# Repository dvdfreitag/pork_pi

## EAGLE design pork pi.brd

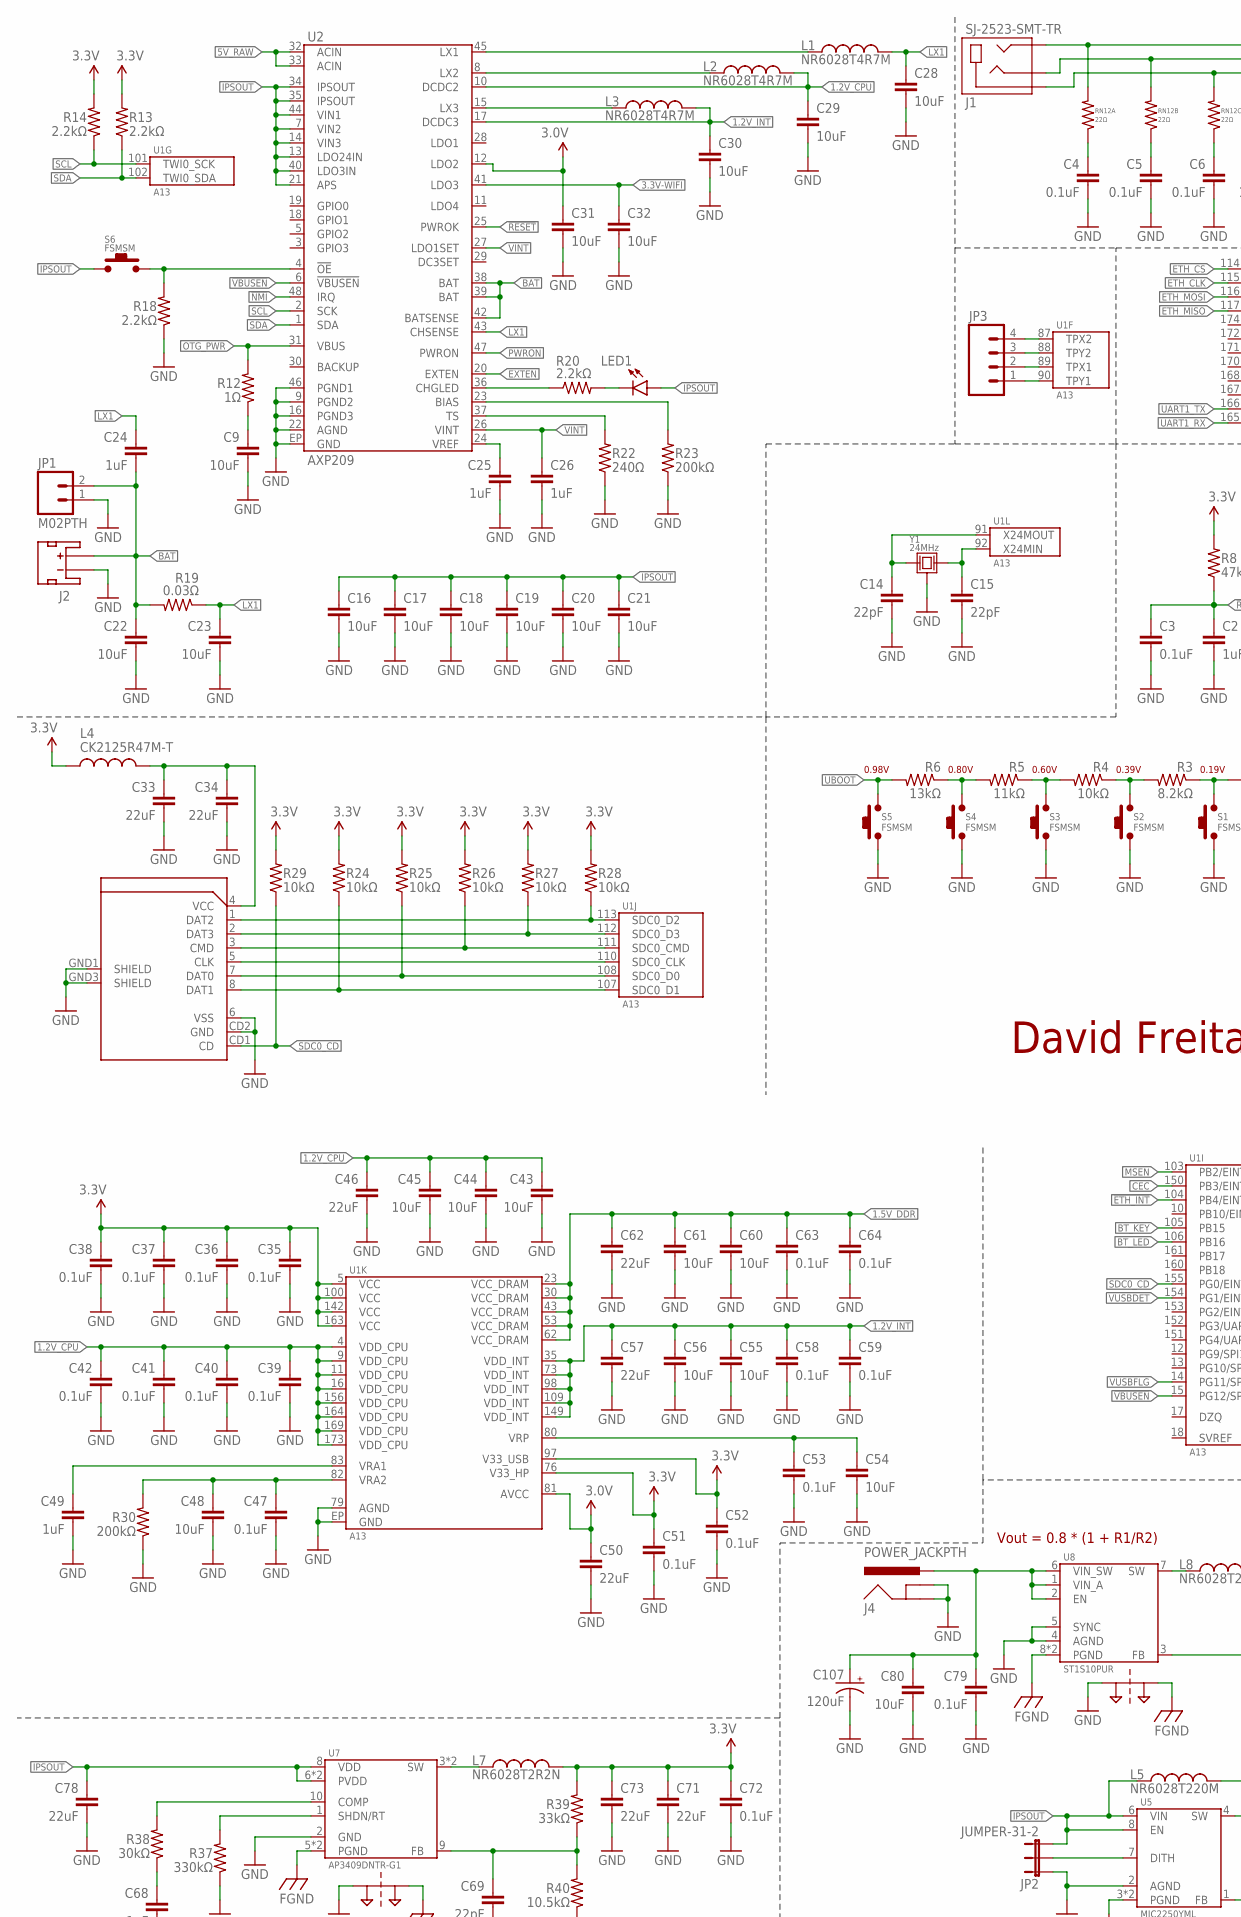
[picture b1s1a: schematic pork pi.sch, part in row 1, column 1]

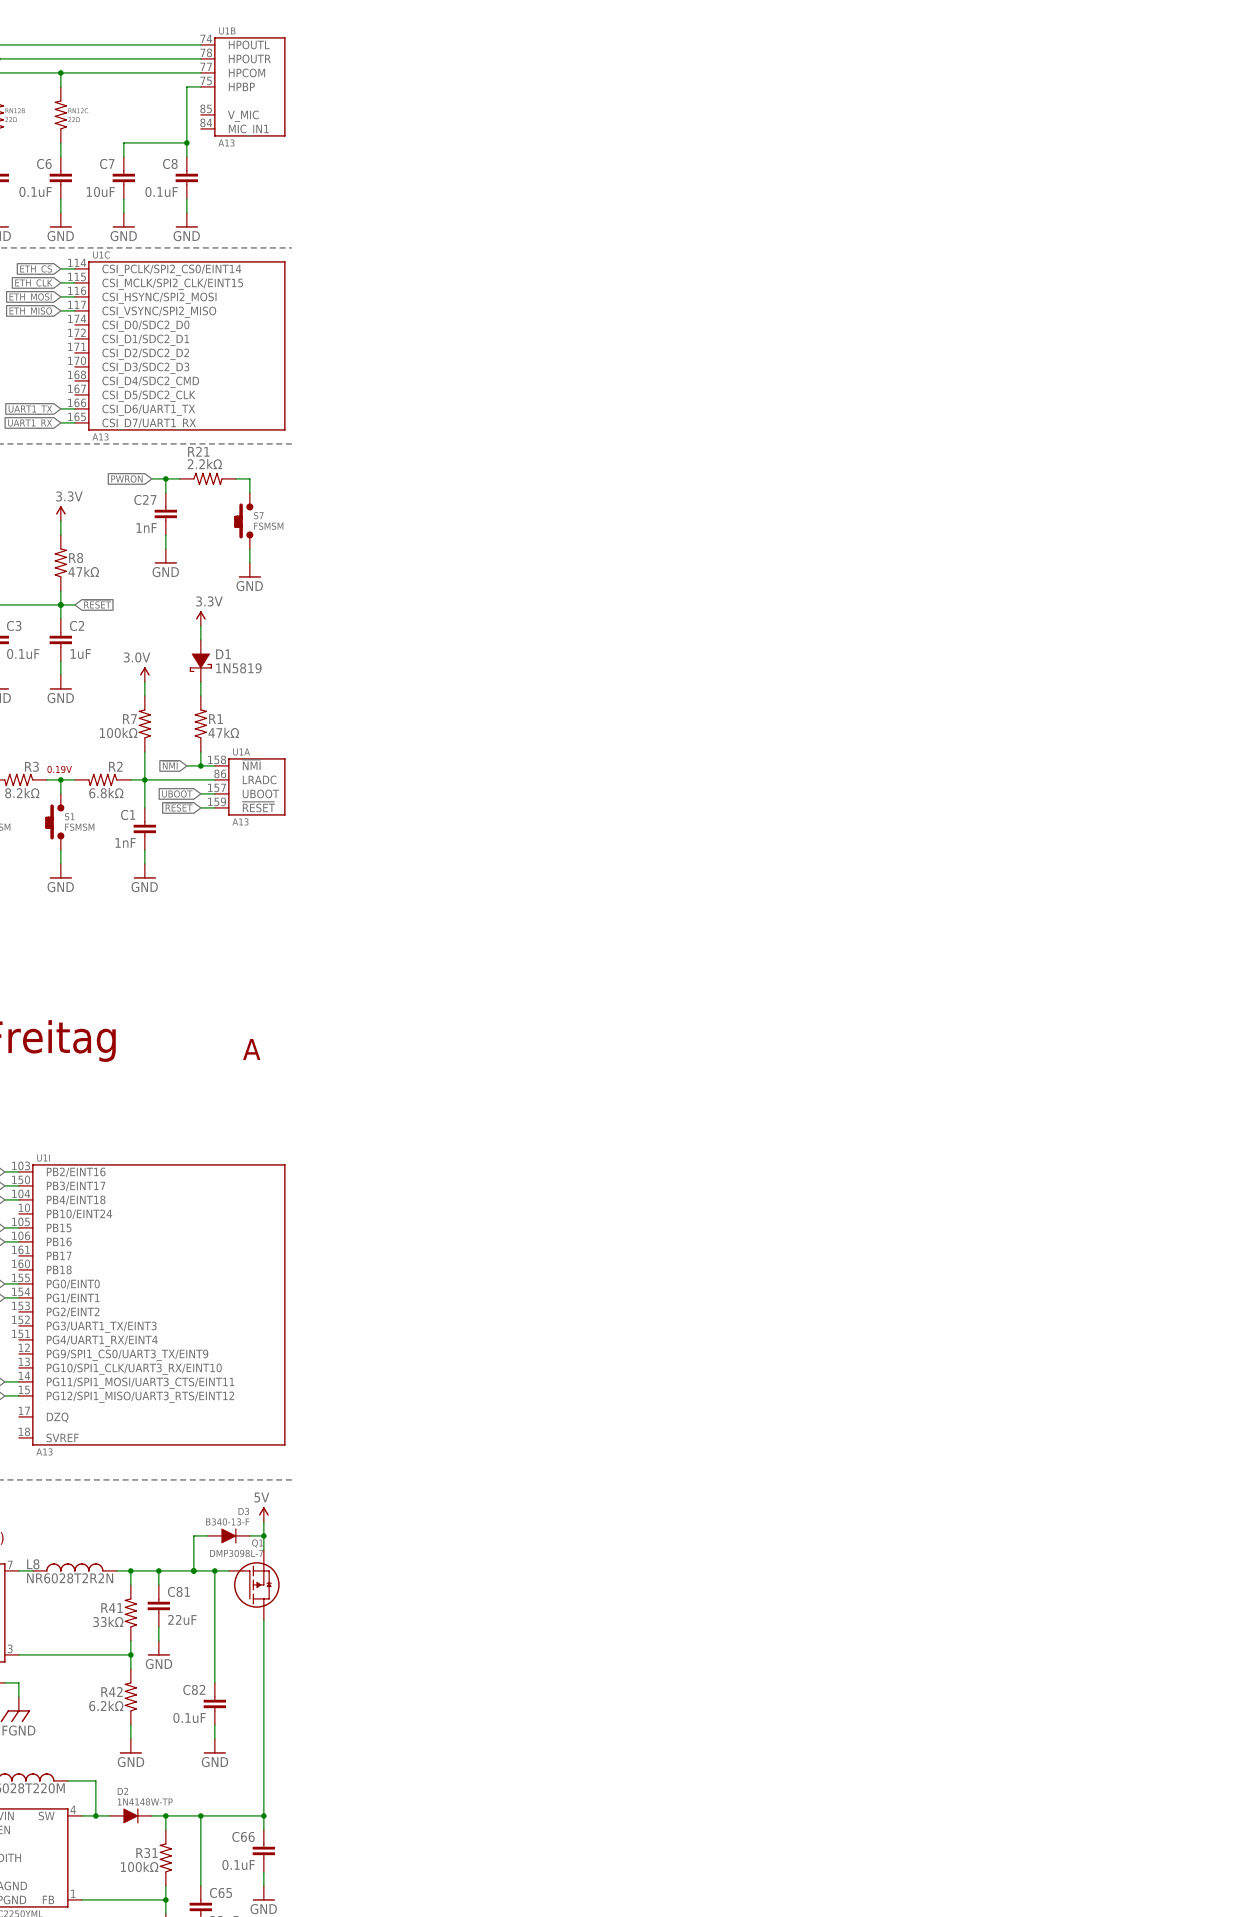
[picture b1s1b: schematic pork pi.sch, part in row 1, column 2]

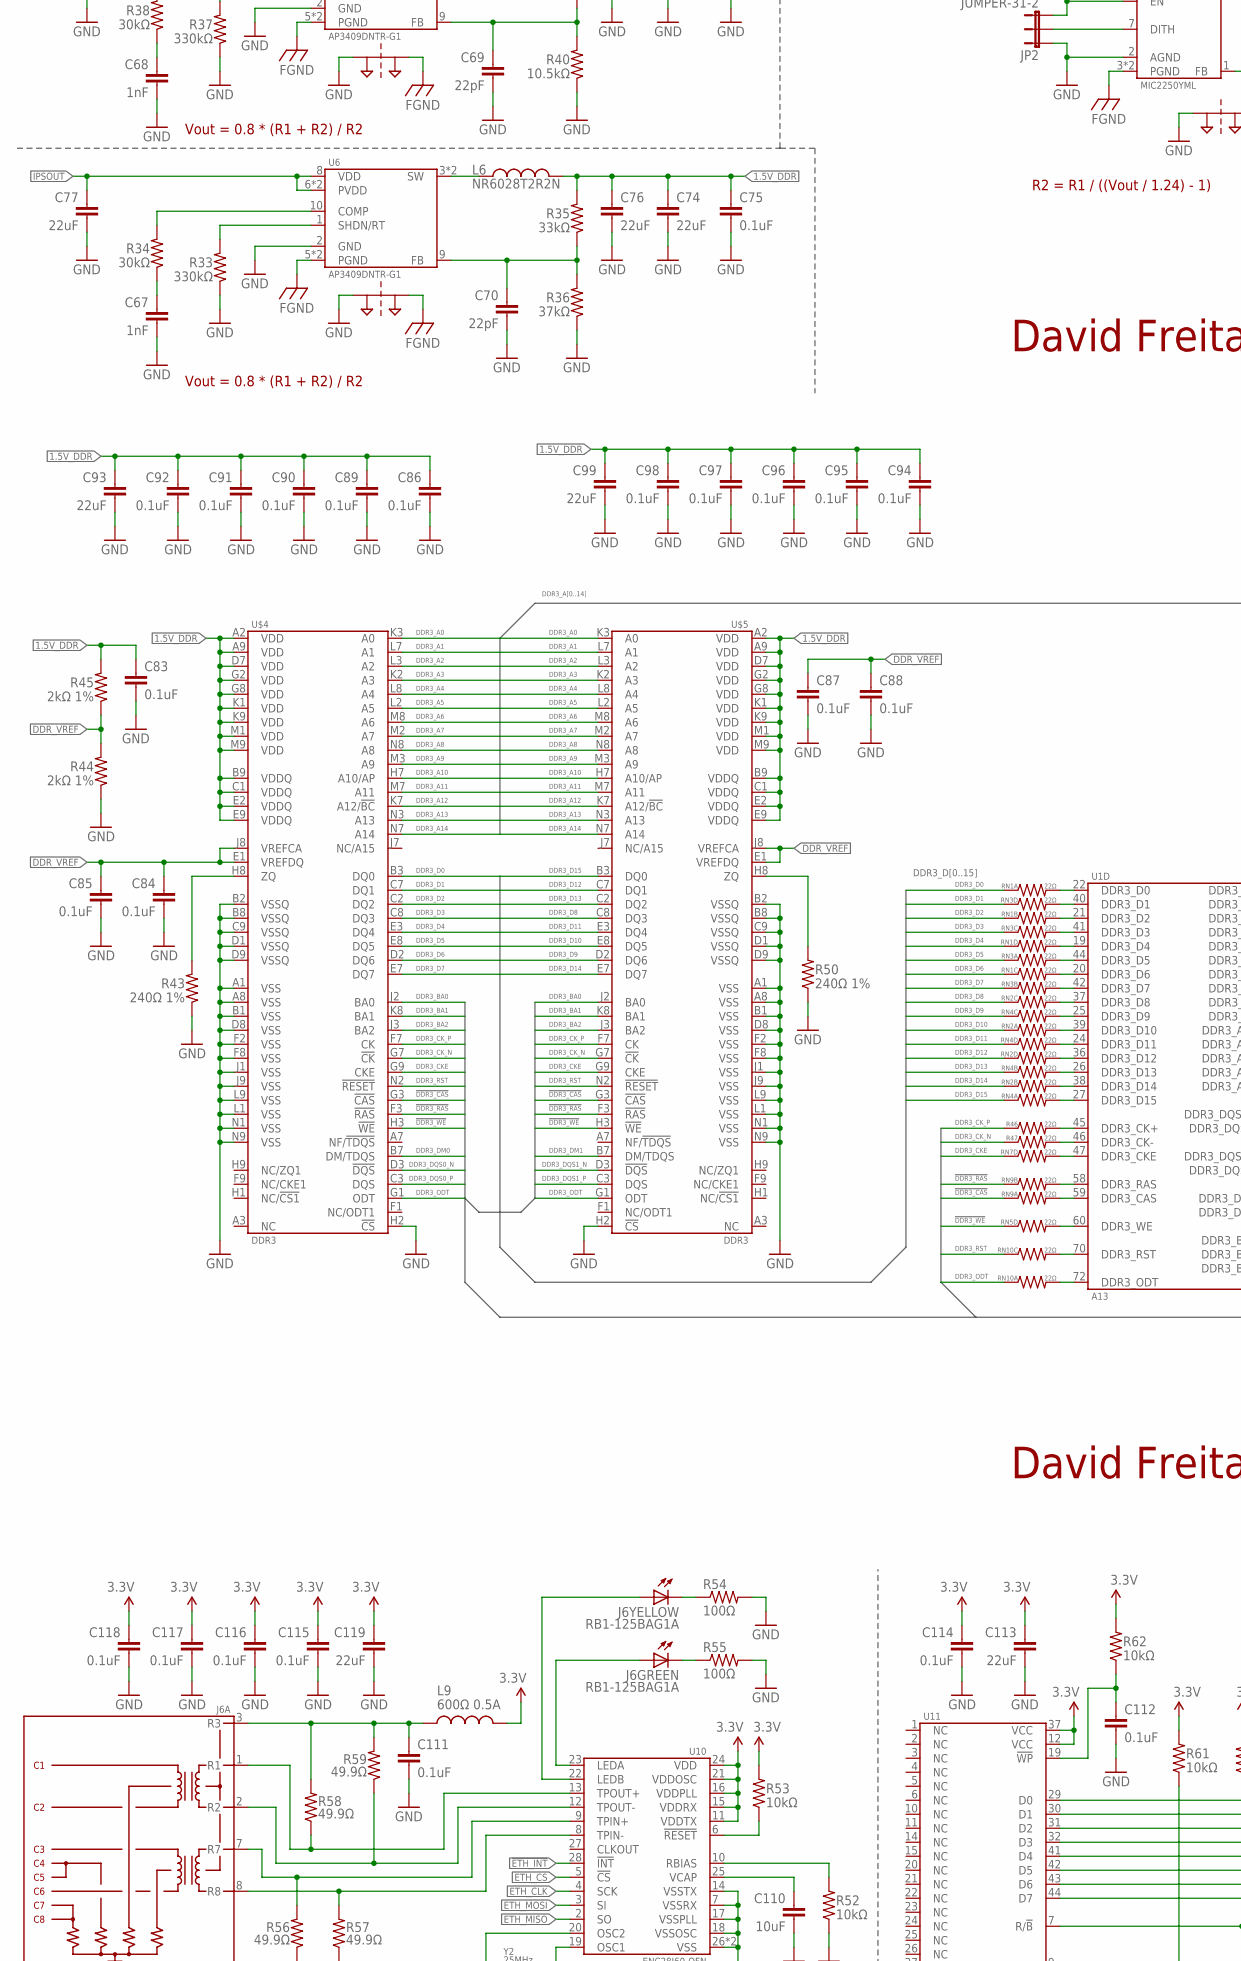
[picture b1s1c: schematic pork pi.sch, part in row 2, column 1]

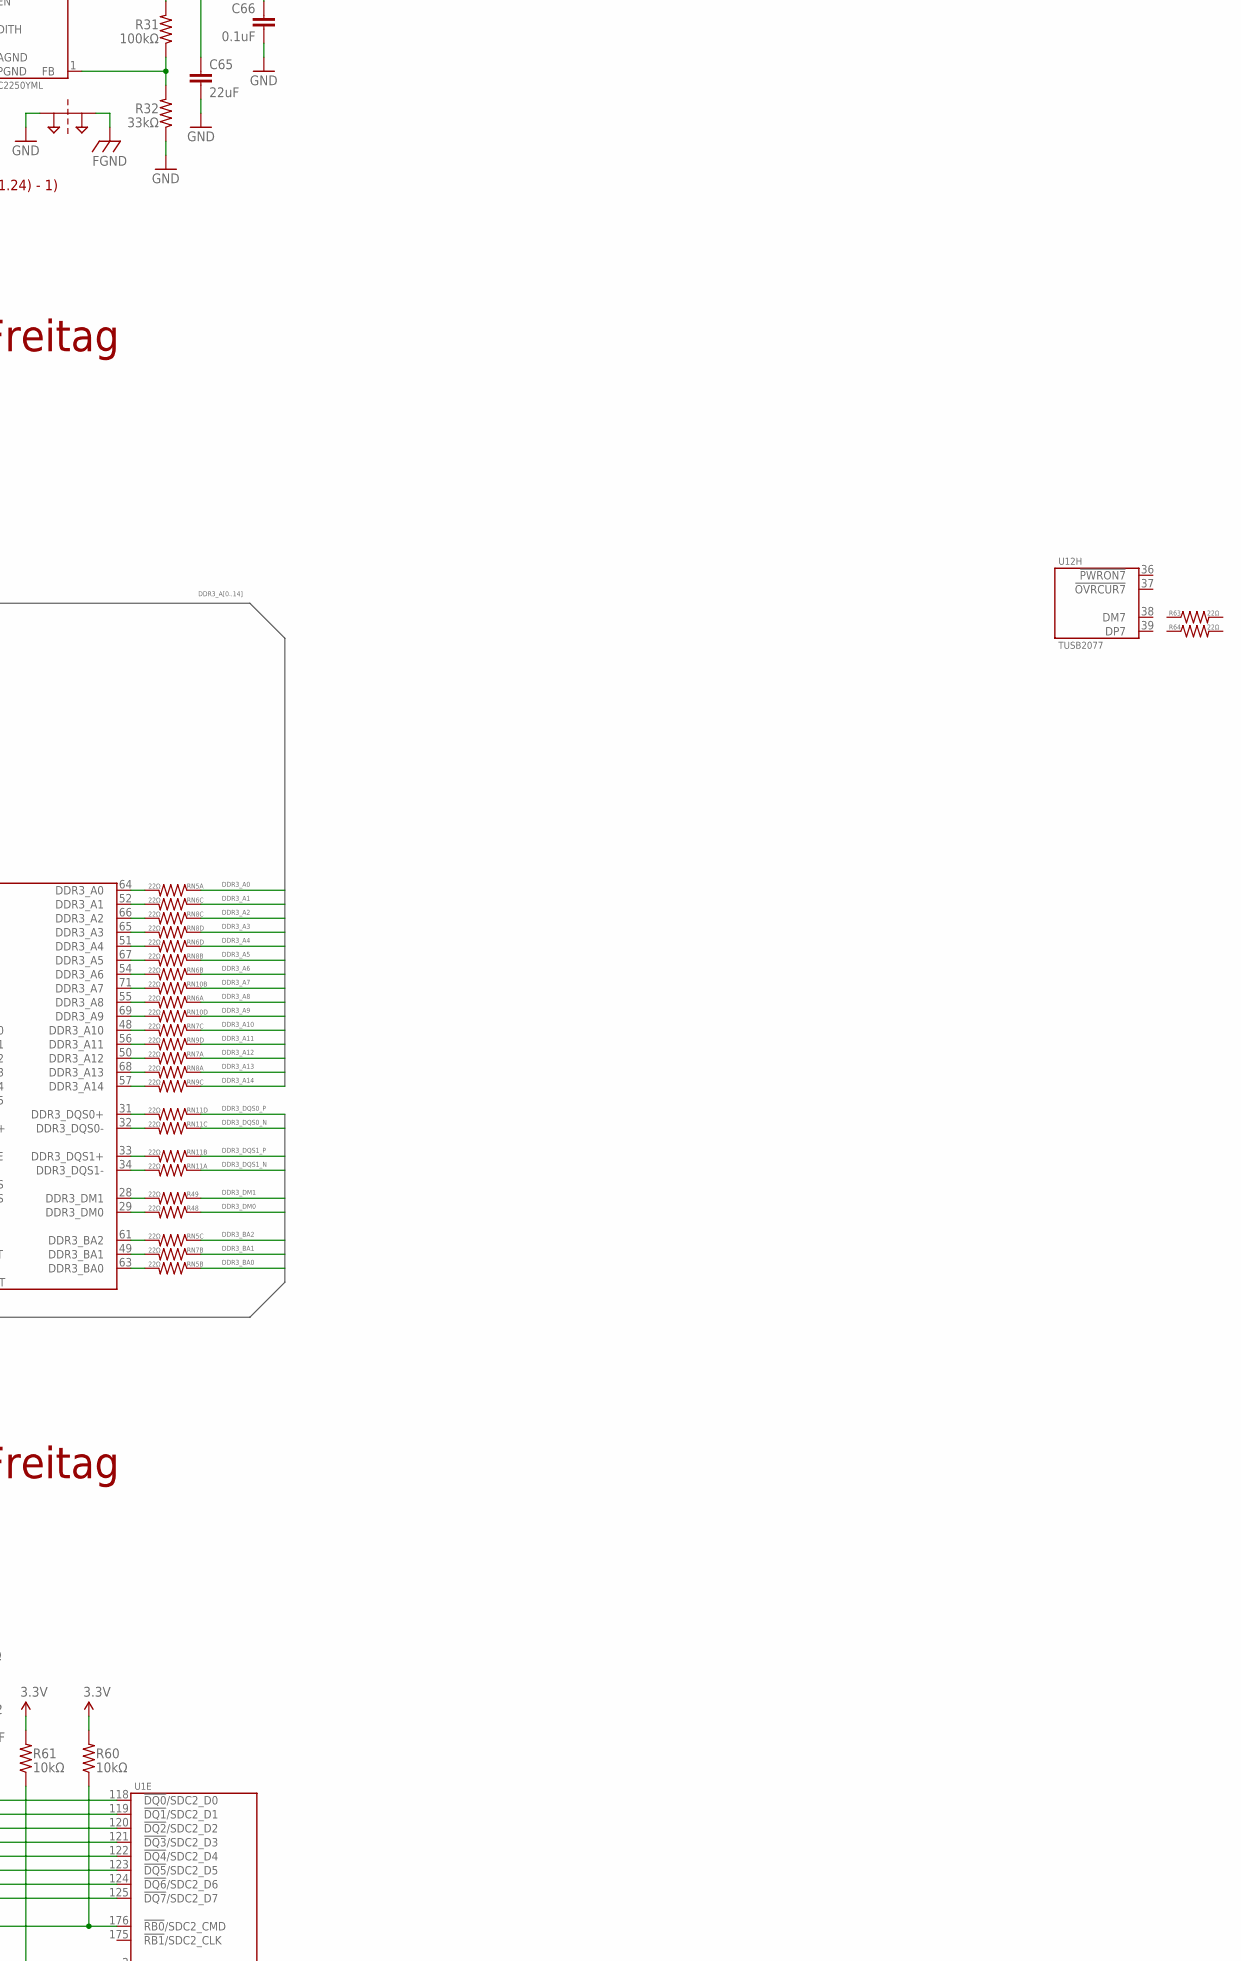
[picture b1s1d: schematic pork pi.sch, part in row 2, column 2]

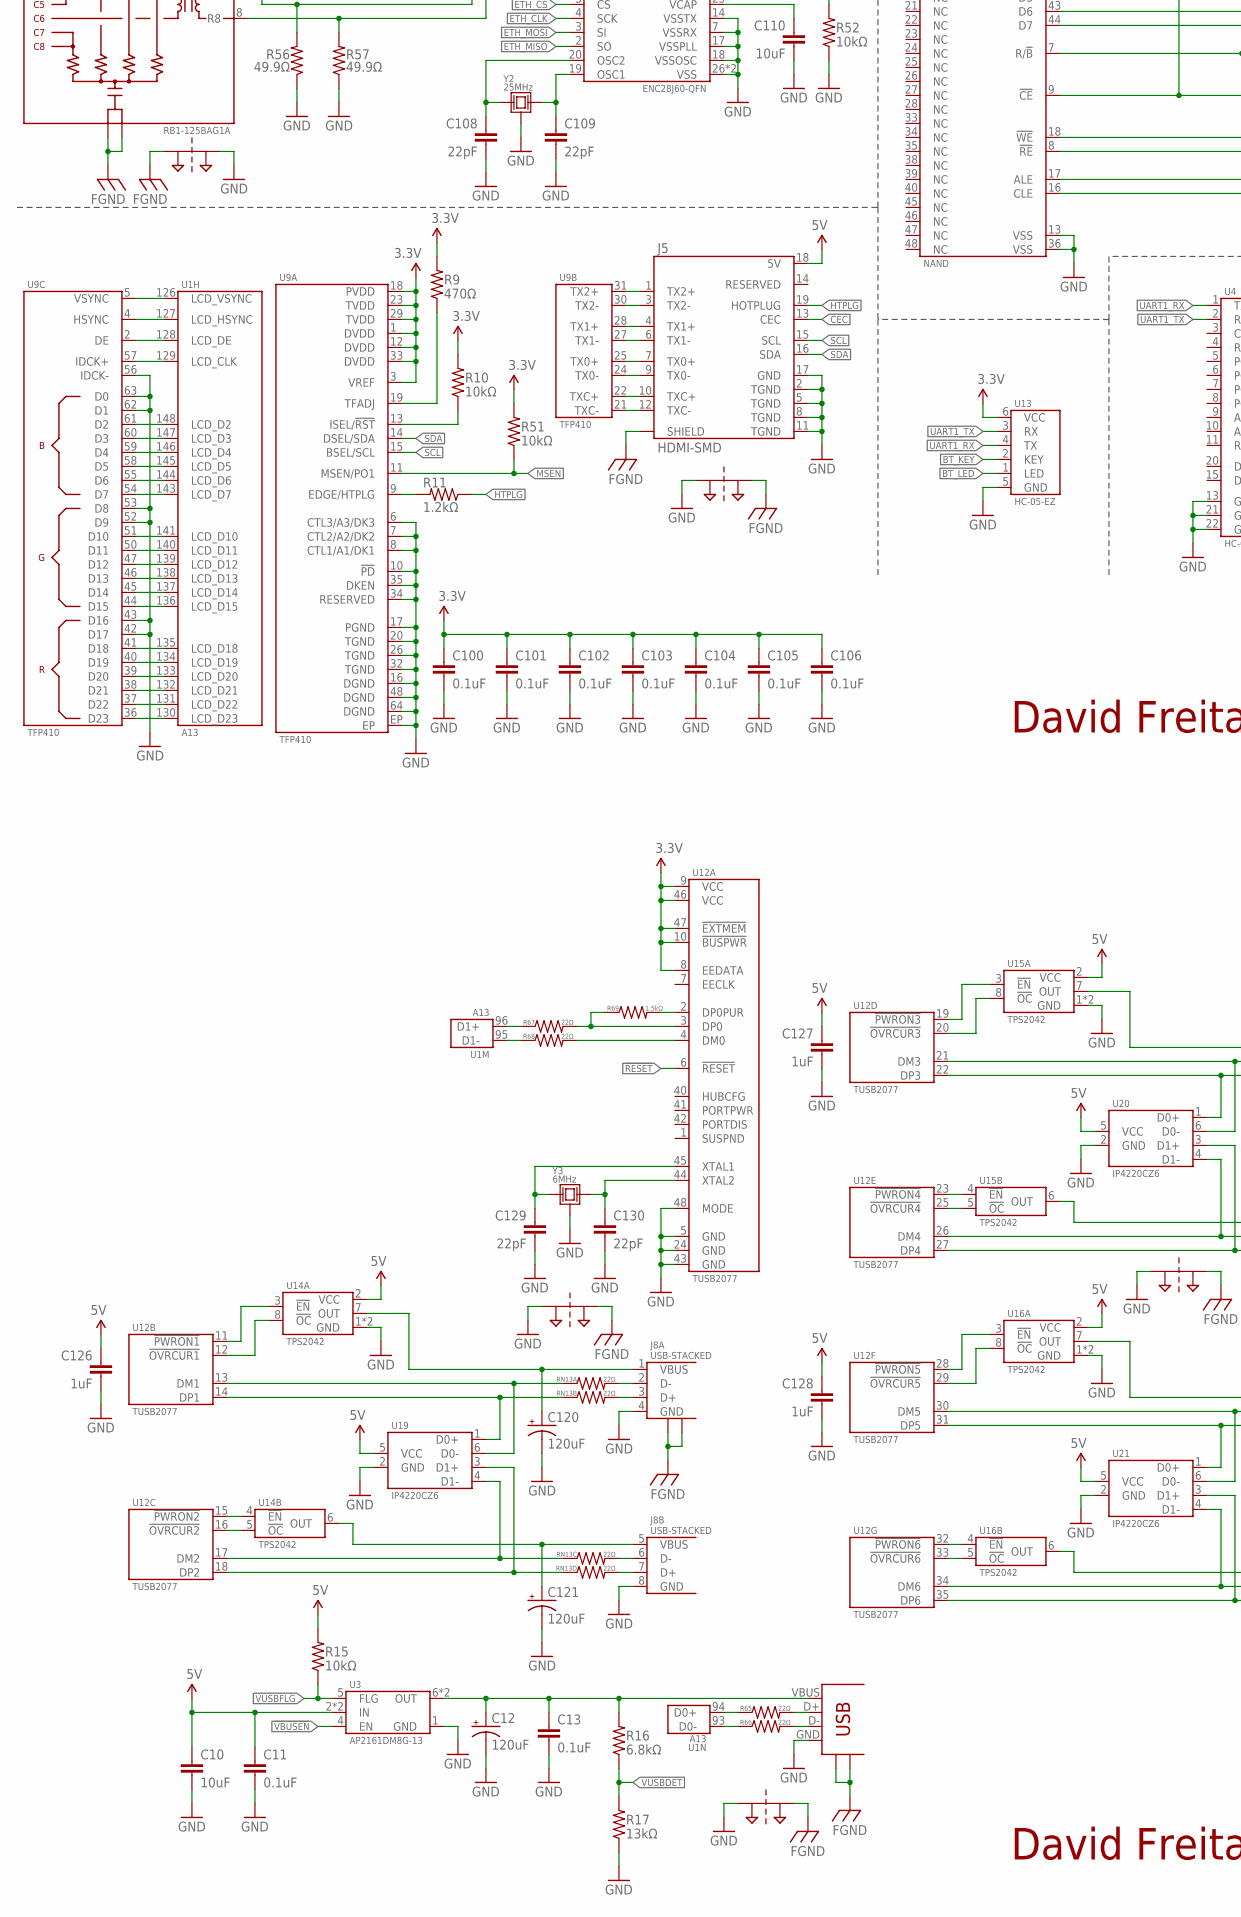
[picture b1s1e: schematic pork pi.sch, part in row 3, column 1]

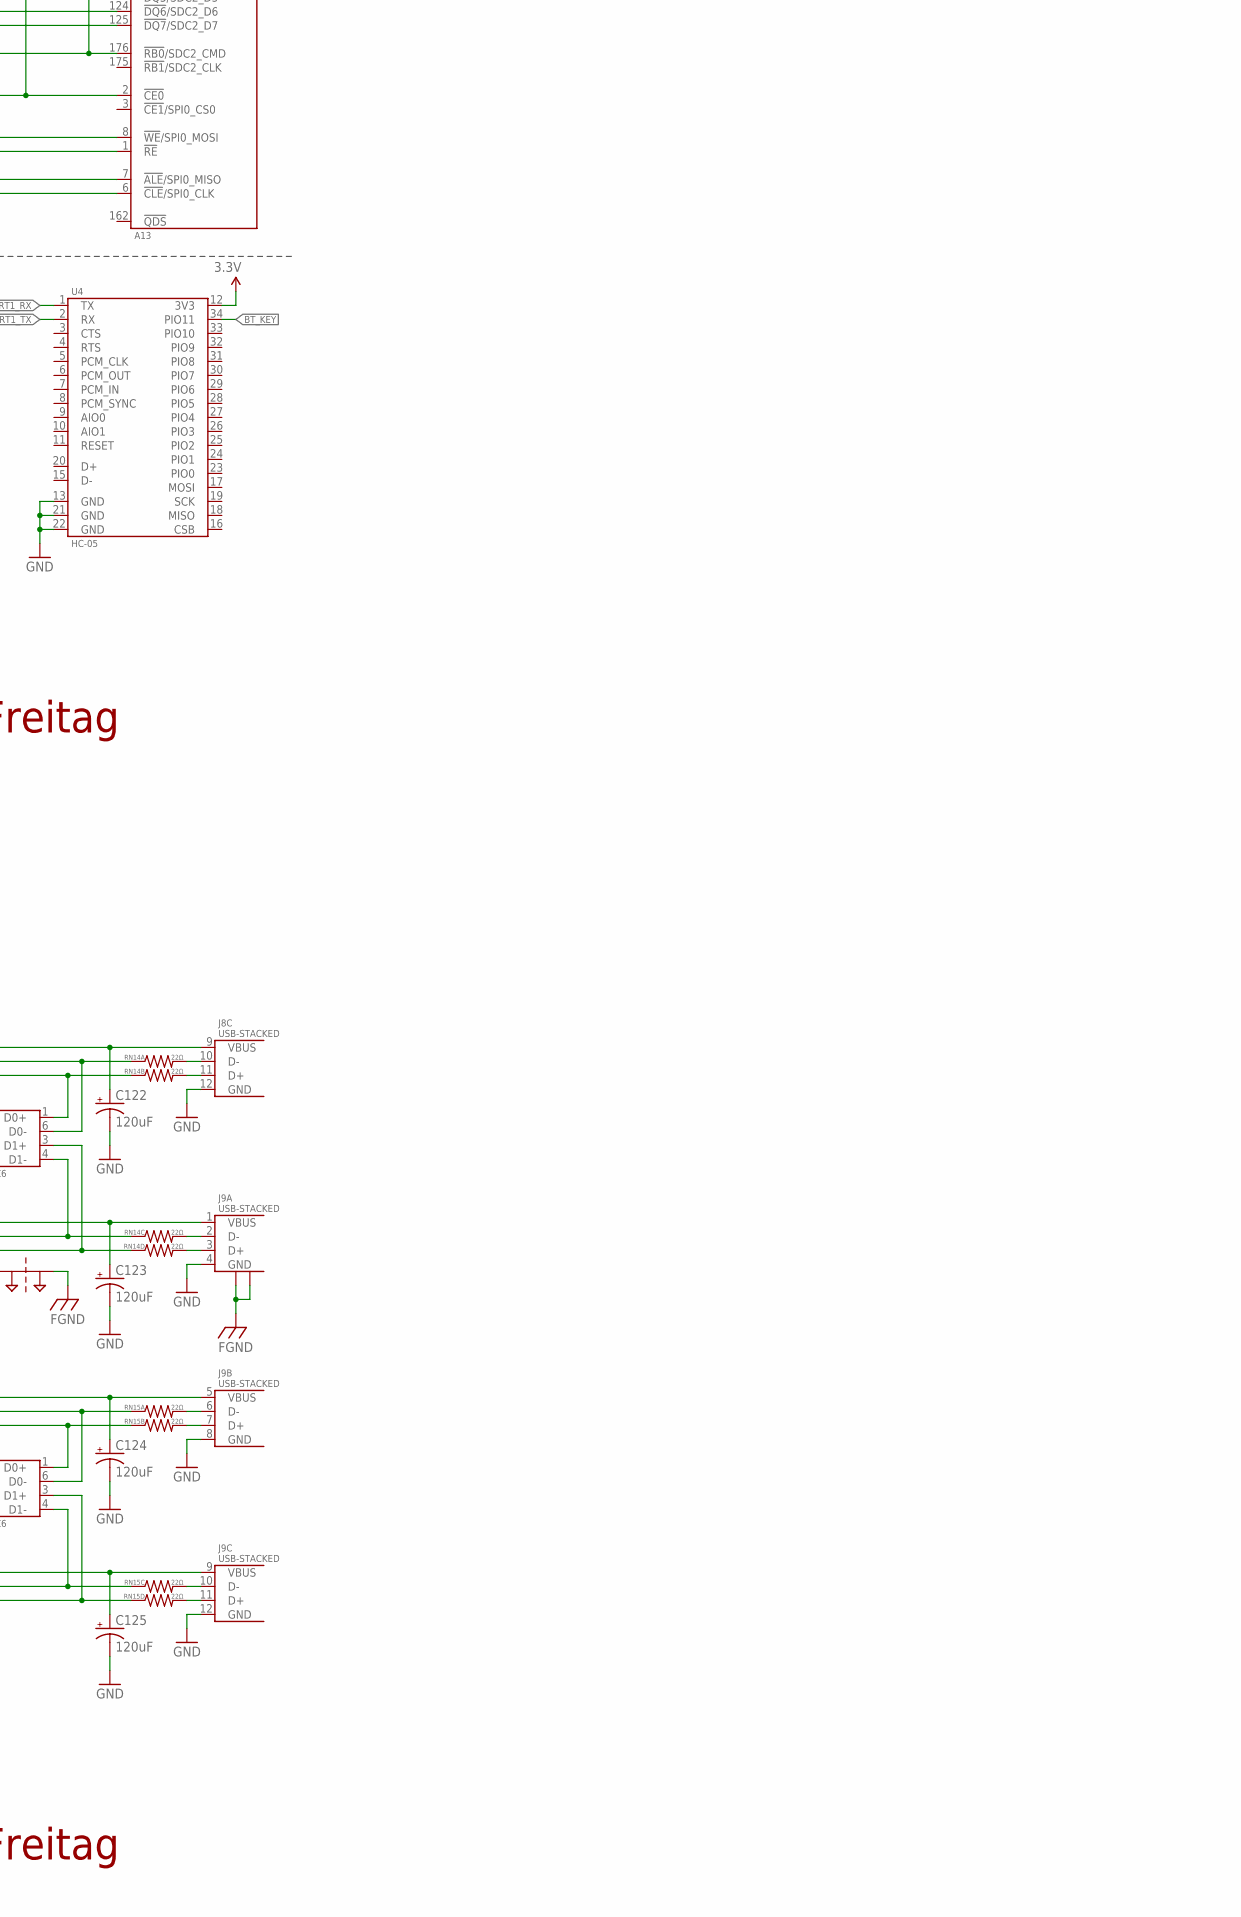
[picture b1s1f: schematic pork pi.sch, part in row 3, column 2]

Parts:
C1, C27, C67, C68: 1nF; 0402-CAP
C2, C24, C25, C26, C49, C126, C127, C128: 1uF; 0402-CAP
C3, C4, C5, C6, C8, C11, C13, C35, C36, C37, C38, C39, C40, C41, C42, C47, C51, C52, C53, C58, C59, C63, C64, C66, C72, C75, C79, C82, C83, C84, C85, C86, C87, C88, C89, C90, C91, C92, C94, C95, C96, C97, C98, C100, C101, C102, C103, C104, C105, C106, C111, C112, C114, C115, C116, C117, C118: 0.1uF; 0402-CAP
C7, C9, C10, C16, C17, C18, C19, C20, C21, C22, C23, C28, C29, C30, C31, C32, C43, C44, C45, C48, C54, C55, C56, C60, C61, C80, C110: 10uF; 0603-CAP
C12, C107, C120, C121, C122, C123, C124, C125: 120uF; CAP_POLYMER-6.5X6.5; PARTNUM 493-7371-1-ND
C14, C15, C69, C70, C108, C109, C129, C130: 22pF; 0402-CAP
C33, C34, C46, C50, C57, C62, C65, C71, C73, C74, C76, C77, C78, C81, C93, C99, C113, C119: 22uF; 0603-CAP
D1: 1N5819; SOD123
D2: 1N4148W-TP; SOD-123
D3: B340-13-F; SMC
J1: SJ-2523-SMT-TR
J2: JST_2MM_MALE; JST-2-SMD
J3: MICRO-SD; MICRO-SD-SOCKET-PP
J4: POWER_JACKPTH; POWER_JACK_PTH
J5: HDMI-SMD
J6: RB1-125BAG1A; ETHERNET
J7: USB+SHIELD-MICROB; USB-MICROB
J8, J9: USB-STACKED
JP1: M02PTH; 1X02
JP2: JUMPER-31-2; SJ_3_PASTE1&2
JP3: M04PTH; 1X04
L1, L2, L3: NR6028T4R7M
L4: CK2125R47M-T; 0805
L5: NR6028T220M; NR6028T4R7M
L6, L7, L8: NR6028T2R2N; NR6028T4R7M
L9: 600Ω 0.5A; 0805
LED1: LED1206; LED-1206
PT1, PT2, PT3, PT4, PT5, PT6, PT7, PT8, PT9: 2PT_GND_TIE
Q1: DMP3098L-7; SOT23-3
R1, R8: 47kΩ; 0402-RES
R2, R16: 6.8kΩ; 0402-RES
R3: 8.2kΩ; 0402-RES
R4, R10, R15, R24, R25, R26, R27, R28, R29, R51, R52, R53, R60, R61, R62: 10kΩ; 0402-RES
R5: 11kΩ; 0402-RES
R6, R17: 13kΩ; 0402-RES
R7, R31: 100kΩ; 0402-RES
R9: 470Ω; 0402-RES
R11: 1.2kΩ; 0402-RES
R12: 1Ω; 0402-RES
R13, R14, R18, R20, R21: 2.2kΩ; 0402-RES
R19: 0.03Ω; 0805
R22: 240Ω; 0402-RES
R23, R30: 200kΩ; 0402-RES
R32, R35, R39, R41: 33kΩ; 0402-RES
R33, R37: 330kΩ; 0402-RES
R34, R38: 30kΩ; 0402-RES
R36: 37kΩ; 0402-RES
R40: 10.5kΩ; 0402-RES
R42: 6.2kΩ; 0402-RES
R43, R50: 240Ω 1%; 0402-RES
R44, R45: 2kΩ 1%; 0402-RES
R46, R47, R48, R49, R63, R64, R65, R66, R67, R68: 22Ω; 0402-RES
R54, R55: 100Ω; 0402-RES
R56, R57, R58, R59: 49.9Ω; 0805
R69: 1.5kΩ; 0402-RES
RN1, RN2, RN3, RN4, RN5, RN6, RN7, RN8, RN9, RN10, RN11, RN12, RN13, RN14, RN15: 22Ω; RESISTOR_NETWORK-1206
S1, S2, S3, S4, S5, S6, S7: FSMSM
U1: A13
U2: AXP209; QFN-48
U3: AP2161DM8G-13; MSOP-8
U4: HC-05
U5: MIC2250YML; MLF-8
U6, U7: AP3409DNTR-G1; UDFN-10
U8: ST1S10PUR; DFN-8
U9: TFP410; PQFP-64
U10: ENC28J60-QFN; QFN-28
U11: NAND; TSOP1-48
U12: TUSB2077; LQFP-48
U13: HC-05-EZ; M06X1
U14, U15, U16: TPS2042; SON-8
U19, U20, U21: IP4220CZ6; SOT-6
U$4, U$5: DDR3; DDR3_78
Y1: 24MHz; FA-238
Y2: 25MHz; FA-238
Y3: 6MHz; FA-238

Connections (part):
1.2V_CPU: C29.1, C39.1, C40.1, C41.1, C42.1, C43.1, C44.1, C45.1, C46.1, L2.2, U1.4 (VDD_CPU), U1.9 (VDD_CPU), U1.11 (VDD_CPU), U1.16 (VDD_CPU), U1.156 (VDD_CPU), U1.164 (VDD_CPU), U1.169 (VDD_CPU), U1.173 (VDD_CPU), U2.10 (DCDC2)
1.2V_INT: C30.1, C55.1, C56.1, C57.1, C58.1, C59.1, L3.2, U1.35 (VDD_INT), U1.73 (VDD_INT), U1.98 (VDD_INT), U1.109 (VDD_INT), U1.149 (VDD_INT), U2.17 (DCDC3)
1.5V_DDR: C60.1, C61.1, C62.1, C63.1, C64.1, C74.1, C75.1, C76.1, C83.1, C86.1, C89.1, C90.1, C91.1, C92.1, C93.1, C94.1, C95.1, C96.1, C97.1, C98.1, C99.1, L6.2, R35.2, R45.2, U1.23 (VCC_DRAM), U1.30 (VCC_DRAM), U1.43 (VCC_DRAM), U1.53 (VCC_DRAM), U1.62 (VCC_DRAM), U$4.A2 (VDD), U$4.A9 (VDD), U$4.B9 (VDDQ), U$4.C1 (VDDQ), U$4.D7 (VDD), U$4.E2 (VDDQ), U$4.E9 (VDDQ), U$4.G2 (VDD), U$4.G8 (VDD), U$4.K1 (VDD), U$4.K9 (VDD), U$4.M1 (VDD), U$4.M9 (VDD), U$5.A2 (VDD), U$5.A9 (VDD), U$5.B9 (VDDQ), U$5.C1 (VDDQ), U$5.D7 (VDD), U$5.E2 (VDDQ), U$5.E9 (VDDQ), U$5.G2 (VDD), U$5.G8 (VDD), U$5.K1 (VDD), U$5.K9 (VDD), U$5.M1 (VDD), U$5.M9 (VDD)
3.0V: C31.1, C50.1, R7.2, U1.81 (AVCC), U2.12 (LDO2)
3.3V: C35.1, C36.1, C37.1, C38.1, C51.1, C52.1, C71.1, C72.1, C73.1, C100.1, C101.1, C102.1, C103.1, C104.1, C105.1, C106.1, C113.1, C114.1, C115.1, C116.1, C117.1, C118.1, C119.1, D1.ANODE, L4.1, L7.2, L9.2, R8.2, R9.2, R10.2, R13.2, R14.2, R24.2, R25.2, R26.2, R27.2, R28.2, R29.2, R39.2, R51.2, R53.2, R60.2, R61.2, R62.2, U1.5 (VCC), U1.76 (V33_HP), U1.97 (V33_USB), U1.100 (VCC), U1.142 (VCC), U1.163 (VCC), U4.12 (3V3), U9.1 (DVDD), U9.3 (VREF), U9.12 (DVDD), U9.18 (PVDD), U9.23 (TVDD), U9.29 (TVDD), U9.33 (DVDD), U10.11 (VDDTX), U10.15 (VDDRX), U10.16 (VDDPLL), U10.21 (VDDOSC), U10.24 (VDD), U11.12 (VCC), U11.37 (VCC), U12.8 (EEDATA), U12.9 (VCC), U12.10 (!BUSPWR), U12.46 (VCC), U12.47 (!EXTMEM), U13.6 (VCC)
3.3V-WIFI: C32.1, U2.41 (LDO3)
5V: C10.1, C11.1, C126.1, C127.1, C128.1, D3.C, J5.18 (5V), Q1.2 (S), R15.2, U3.2 (IN), U3.3 (IN), U14.2 (VCC), U15.2 (VCC), U16.2 (VCC), U19.5 (VCC), U20.5 (VCC), U21.5 (VCC)
5V_RAW: U2.32 (ACIN), U2.33 (ACIN)
!DDR3_CAS!: RN9.1, U$4.G3 (!CAS), U$5.G3 (!CAS)
!DDR3_RAS!: RN9.2 (1), U$4.F3 (!RAS), U$5.F3 (!RAS)
!DDR3_WE!: RN5.4 (1), U$4.H3 (!WE), U$5.H3 (!WE)
!ETH_INT: U1.104 (PB4/EINT18), U10.28 (!INT)
!NMI: R1.1, U1.158 (!NMI), U2.48 (IRQ)
!RESET: C2.1, C3.1, R8.1, U1.159 (!RESET), U2.25 (PWROK), U12.6 (!RESET)
!VBUSEN: U1.15 (PG12/SPI1_MISO/UART3_RTS/EINT12), U2.6 (!VBUSEN), U3.4 (EN)
BAT: C22.1, C24.2, J2.2 (+), JP1.2, R19.2, U2.38 (BAT), U2.39 (BAT), U2.42 (BATSENSE)
BT_KEY: U1.105 (PB15), U4.34 (PIO11), U13.2 (KEY)
BT_LED: U1.106 (PB16), U13.1 (LED)
CEC: J5.13 (CEC), U1.150 (PB3/EINT17)
D0_N: R66.1, U1.93 (D0-)
D0_P: R65.1, U1.94 (D0+)
D1_N: R68.1, U1.95 (D1-)
D1_P: R67.1, U1.96 (D1+)
D2_N: RN13.1, U12.13 (DM1), U19.6 (D0-)
D2_P: RN13.2 (1), U12.14 (DP1), U19.1 (D0+)
D3_N: RN13.3 (1), U12.17 (DM2), U19.4 (D1-)
D3_P: RN13.4 (1), U12.18 (DP2), U19.3 (D1+)
D4_N: RN14.1, U12.21 (DM3), U20.6 (D0-)
D4_P: RN14.2 (1), U12.22 (DP3), U20.1 (D0+)
D5_N: RN14.3 (1), U12.26 (DM4), U20.4 (D1-)
D5_P: RN14.4 (1), U12.27 (DP4), U20.3 (D1+)
D6_N: RN15.1, U12.30 (DM5), U21.6 (D0-)
D6_P: RN15.2 (1), U12.31 (DP5), U21.1 (D0+)
D7_N: RN15.3 (1), U12.34 (DM6), U21.4 (D1-)
D7_P: RN15.4 (1), U12.35 (DP6), U21.3 (D1+)
DDR3_A0: RN5.1, U$4.K3 (A0), U$5.K3 (A0)
DDR3_A1: RN6.3 (1), U$4.L7 (A1), U$5.L7 (A1)
DDR3_A2: RN8.3 (1), U$4.L3 (A2), U$5.L3 (A2)
DDR3_A3: RN8.4 (1), U$4.K2 (A3), U$5.K2 (A3)
DDR3_A4: RN6.4 (1), U$4.L8 (A4), U$5.L8 (A4)
DDR3_A5: RN8.2 (1), U$4.L2 (A5), U$5.L2 (A5)
DDR3_A6: RN6.2 (1), U$4.M8 (A6), U$5.M8 (A6)
DDR3_A7: RN10.2 (1), U$4.M2 (A7), U$5.M2 (A7)
DDR3_A8: RN6.1, U$4.N8 (A8), U$5.N8 (A8)
DDR3_A9: RN10.4 (1), U$4.M3 (A9), U$5.M3 (A9)
DDR3_A10: RN7.3 (1), U$4.H7 (A10/AP), U$5.H7 (A10/AP)
DDR3_A11: RN9.4 (1), U$4.M7 (A11), U$5.M7 (A11)
DDR3_A12: RN7.1, U$4.K7 (A12/!BC), U$5.K7 (A12/!BC)
DDR3_A13: RN8.1, U$4.N3 (A13), U$5.N3 (A13)
DDR3_A14: RN9.3 (1), U$4.N7 (A14), U$5.N7 (A14)
DDR3_BA0: RN5.2 (1), U$4.J2 (BA0), U$5.J2 (BA0)
DDR3_BA1: RN7.2 (1), U$4.K8 (BA1), U$5.K8 (BA1)
DDR3_BA2: RN5.3 (1), U$4.J3 (BA2), U$5.J3 (BA2)
DDR3_CKE: RN7.4 (1), U$4.G9 (CKE), U$5.G9 (CKE)
DDR3_CK_N: R47.1, U$4.G7 (!CK), U$5.G7 (!CK)
DDR3_CK_P: R46.1, U$4.F7 (CK), U$5.F7 (CK)
DDR3_D0: RN1.1, U$4.B3 (DQ0)
DDR3_D1: RN3.4 (1), U$4.C7 (DQ1)
DDR3_D2: RN1.2 (1), U$4.C2 (DQ2)
DDR3_D3: RN3.3 (1), U$4.C8 (DQ3)
DDR3_D4: RN1.4 (1), U$4.E3 (DQ4)
DDR3_D5: RN3.1, U$4.E8 (DQ5)
DDR3_D6: RN1.3 (1), U$4.D2 (DQ6)
DDR3_D7: RN3.2 (1), U$4.E7 (DQ7)
DDR3_D8: RN2.3 (1), U$5.C8 (DQ3)
DDR3_D9: RN4.3 (1), U$5.D2 (DQ6)
DDR3_D10: RN2.1, U$5.E8 (DQ5)
DDR3_D11: RN4.4 (1), U$5.E3 (DQ4)
DDR3_D12: RN2.4 (1), U$5.C7 (DQ1)
DDR3_D13: RN4.2 (1), U$5.C2 (DQ2)
DDR3_D14: RN2.2 (1), U$5.E7 (DQ7)
DDR3_D15: RN4.1, U$5.B3 (DQ0)
DDR3_DM0: R48.1, U$4.B7 (DM/TDQS)
DDR3_DM1: R49.1, U$5.B7 (DM/TDQS)
DDR3_DQS0_N: RN11.3 (1), U$4.D3 (!DQS)
DDR3_DQS0_P: RN11.4 (1), U$4.C3 (DQS)
DDR3_DQS1_N: RN11.1, U$5.D3 (!DQS)
DDR3_DQS1_P: RN11.2 (1), U$5.C3 (DQS)
DDR3_ODT: RN10.1, U$4.G1 (ODT), U$5.G1 (ODT)
DDR3_RST: RN10.3 (1), U$4.N2 (!RESET), U$5.N2 (!RESET)
DDR_VREF: C84.1, C85.1, C87.1, C88.1, R44.2, R45.1, U$4.E1 (VREFDQ), U$4.J8 (VREFCA), U$5.E1 (VREFDQ), U$5.J8 (VREFCA)
ETH_CLK: U1.115 (CSI_MCLK/SPI2_CLK/EINT15), U10.4 (SCK)
ETH_CS: U1.114 (CSI_PCLK/SPI2_CS0/EINT14), U10.5 (!CS)
ETH_MISO: U1.117 (CSI_VSYNC/SPI2_MISO), U10.2 (SO)
ETH_MOSI: U1.116 (CSI_HSYNC/SPI2_MOSI), U10.3 (SI)
EXTEN: U2.20 (EXTEN)
FGND: J5.P$1 (SHIELD), J5.P$2 (SHIELD), J5.P$3 (SHIELD), J5.P$4 (SHIELD), J6.P$5, J6.P$6, J7.MT1 (S1), J7.MT2 (S2), J7.P$1 (S1), J7.P$2 (S2), J8.P$1, J8.P$2, J8.P$3, J8.P$4, J9.P$1, J9.P$2, J9.P$3, J9.P$4, PT1.P$2, PT2.P$2, PT3.P$2, PT4.P$2, PT5.P$2, PT6.P$2, PT7.P$2, PT8.P$2, PT9.P$2, U5.3 (PGND), U5.EP (PGND), U6.5 (PGND), U6.EP (PGND), U7.5 (PGND), U7.EP (PGND), U8.8 (PGND), U8.EP (PGND)
GND: C1.2, C2.2, C3.2, C4.2, C5.2, C6.2, C7.2, C8.2, C9.2, C10.2, C11.2, C12.-, C13.2, C14.2, C15.2, C16.2, C17.2, C18.2, C19.2, C20.2, C21.2, C22.2, C23.2, C25.2, C26.2, C27.2, C28.2, C29.2, C30.2, C31.2, C32.2, C33.2, C34.2, C35.2, C36.2, C37.2, C38.2, C39.2, C40.2, C41.2, C42.2, C43.2, C44.2, C45.2, C46.2, C47.2, C48.2, C49.2, C50.2, C51.2, C52.2, C53.2, C54.2, C55.2, C56.2, C57.2, C58.2, C59.2, C60.2, C61.2, C62.2, C63.2, C64.2, C65.2, C66.2, C67.2, C68.2, C69.2, C70.2, C71.2, C72.2, C73.2, C74.2, C75.2, C76.2, C77.2, C78.2, C79.2, C80.2, C81.2, C82.2, C83.2, C84.2, C85.2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
HTPLG: J5.19 (HOTPLUG), R11.1
IPSOUT: C16.1, C17.1, C18.1, C19.1, C20.1, C21.1, C77.1, C78.1, JP2.3, L5.1, LED1.A, S6.P$1, U2.7 (VIN2), U2.13 (LDO24IN), U2.14 (VIN3), U2.21 (APS), U2.34 (IPSOUT), U2.35 (IPSOUT), U2.40 (LDO3IN), U2.44 (VIN1), U5.6 (VIN), U5.8 (EN), U6.6 (PVDD), U6.7 (PVDD), U6.8 (VDD), U7.6 (PVDD), U7.7 (PVDD), U7.8 (VDD)
LX1: C23.1, C24.1, C28.1, L1.2, R19.1, U2.43 (CHSENSE)
MSEN: R51.1, U1.103 (PB2/EINT16), U9.11 (MSEN/PO1)
unnamed: C15.1, U1.92 (X24MIN), Y1.3 (2)
unnamed: D1.CATHODE, R1.2
unnamed: C1.1, R2.1, R7.1, U1.86 (LRADC)
unnamed: R2.2, R3.1, S1.P$2
unnamed: R3.2, R4.1, S2.P$2
unnamed: R4.2, R5.1, S3.P$2
unnamed: R5.2, R6.1, S4.P$2
unnamed: J1.2 (TIP), RN12.5 (2), U1.74 (HPOUTL)
unnamed: J1.3 (RING), RN12.6 (2), U1.78 (HPOUTR)
unnamed: J1.1 (SLEEVE), RN12.7 (2), U1.77 (HPCOM)
unnamed: C4.1, RN12.1
unnamed: C5.1, RN12.2 (1)
unnamed: C6.1, RN12.3 (1)
unnamed: C7.1, C8.1, U1.75 (HPBP)
unnamed: C9.1, R12.1
unnamed: C14.1, U1.91 (X24MOUT), Y1.1
unnamed: R18.2, S6.P$2, U2.4 (!OE)
unnamed: R22.2, U2.37 (TS)
unnamed: C25.1, U2.24 (VREF)
unnamed: R21.2, S7.P$2
unnamed: LED1.C, R20.2
unnamed: R23.2, U2.23 (BIAS)
unnamed: L1.1, U2.45 (LX1)
unnamed: L2.1, U2.8 (LX2)
unnamed: J3.8 (DAT1), R24.1, U1.107 (SDC0_D1)
unnamed: L3.1, U2.15 (LX3)
unnamed: J3.7 (DAT0), R25.1, U1.108 (SDC0_D0)
unnamed: J3.5 (CLK), U1.110 (SDC0_CLK)
unnamed: J3.3 (CMD), R26.1, U1.111 (SDC0_CMD)
unnamed: J3.2 (DAT3), R27.1, U1.112 (SDC0_D3)
unnamed: J3.1 (DAT2), R28.1, U1.113 (SDC0_D2)
unnamed: C49.1, U1.83 (VRA1)
unnamed: C33.1, C34.1, J3.4 (VCC), L4.2
unnamed: C47.1, C48.1, R30.2, U1.82 (VRA2)
unnamed: R20.1, U2.36 (CHGLED)
unnamed: C53.1, C54.1, U1.80 (VRP)
unnamed: JP2.2, U5.7 (DITH)
unnamed: D2.2, L5.2, U5.4 (SW)
unnamed: R31.1, R32.2, U5.1 (FB)
unnamed: C65.1, C66.1, D2.1, Q1.3 (D), R31.2
unnamed: R43.2, U$4.H8 (ZQ)
unnamed: R33.2, U6.1 (SHDN/RT)
unnamed: C67.1, R34.1
unnamed: R34.2, U6.10 (COMP)
unnamed: R37.2, U7.1 (SHDN/RT)
unnamed: C68.1, R38.1
unnamed: R38.2, U7.10 (COMP)
unnamed: L7.1, U7.3 (SW), U7.4 (SW)
unnamed: C79.1, C80.1, C107.+, J4.PWR, U8.1 (VIN_A), U8.2 (EN), U8.6 (VIN_SW)
unnamed: C69.1, R39.1, R40.2, U7.9 (FB)
unnamed: L6.1, U6.3 (SW), U6.4 (SW)
unnamed: L8.1, U8.7 (SW)
unnamed: C70.1, R35.1, R36.2, U6.9 (FB)
unnamed: C81.1, C82.1, D3.A, L8.2, Q1.1 (G), R41.2
unnamed: R41.1, R42.2, U8.3 (FB)
unnamed: RN1.5 (2), U1.22 (DDR3_D0)
unnamed: RN1.6 (2), U1.21 (DDR3_D2)
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
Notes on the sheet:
David Freitag
0.19V
0.39V
0.60V
0.80V
0.98V
R2 = R1 / ((Vout / 1.24) - 1)
Vout = 0.8 * (R1 + R2) / R2
Vout = 0.8 * (1 + R1/R2)

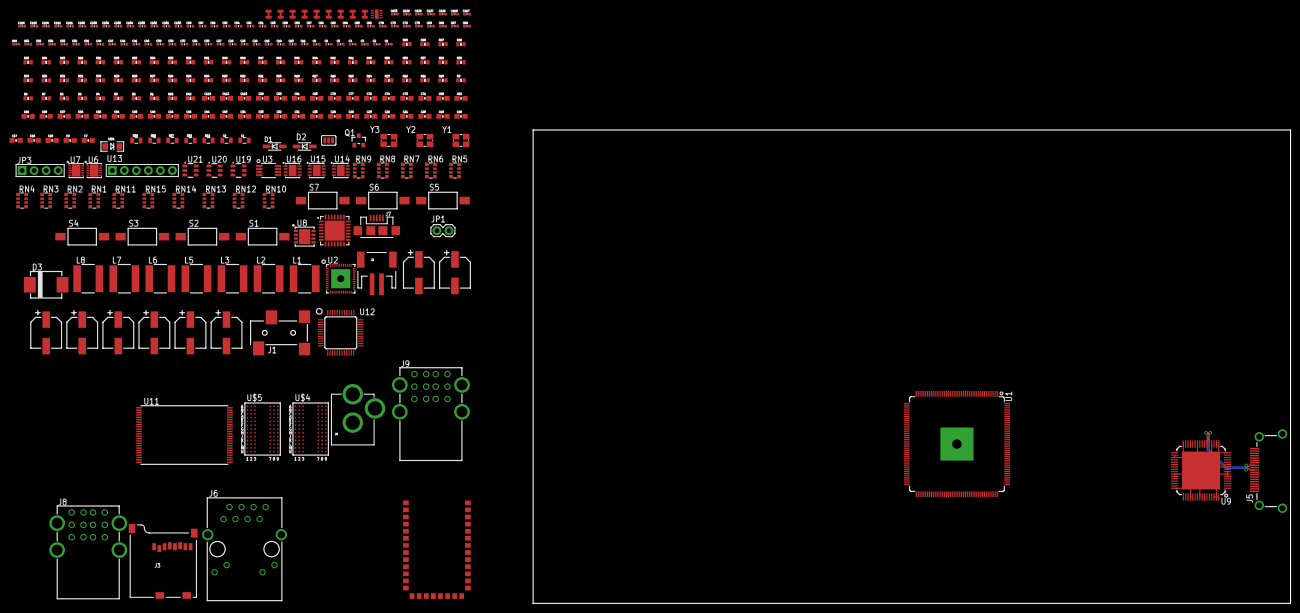
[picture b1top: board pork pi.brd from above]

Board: 2 copper layers, 160.0 x 100.0 mm, 280 parts (0 on the bottom side), 310 nets.

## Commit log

2014-09-29 :neckbeard: Added .gitattributes & .gitignore files
2014-09-29 Upated gitignore
    Added eagle schematic and board history files to gitignore
2014-09-29 Schematic update
    Added LRADC/UBOOT configuration buttons and audio
2014-09-29 Schematic update
    Added other gates for U1
2014-09-30 Schematic update
    Fixed U1 GPIO gate
2014-10-01 Update schematic
    Added AXP209 and began routing power management signals
2014-10-01 Schematic update
    Added more signals to AXP209 including inductors
2014-10-04 Schematic update
    Added SD card as well as decoupling for main cpu
2014-10-05 Schematic update
    Added 3.3V and 1.5V ddr3 switching regulators and all necessary
    inductors and other passives.
2014-10-12 Update gitignore
    fixed typo under Eagle CAD in gitignore
2014-10-12 Schematic update
    Added SK HYNIX 2Gb DD3 chips and necessary signals
2014-10-12 Added reference
    Added Olimex reference design. More info:
    https://github.com/OLIMEX/OLINUXINO
2014-10-12 Added documents
    Added SK HYNIX 2Gb datasheet as well as some reference schematics
2014-10-13 Schematic Update
    Added HDMI controller and required components
2014-10-17 Added document
    Added pdf datasheet for Samsung NAND flash chip
2014-10-17 Add document
    Added document for Diodes AP2161 USB power switch
2014-10-17 Added document
    Added document for AP3409 step-down switching regulator
2014-10-17 Added document
    Added document for X-Powers PMIC
2014-10-17 Added document
    Added document for Microchip ENC28J60 Ethernet controller
2014-10-17 Added document
    Added document for HC-05 bluetooth serial board
2014-10-17 Added document
    Added document for Micrel MIC2250 step-up boost converter
2014-10-17 Added document
    Added document for Ethernet connector
2014-10-17 Added document
    Added document for ST Microelectronics ST1S10
2014-10-17 Added document
    Added document for TI TFP410 HDMI-over-DVI controller
2014-10-17 Added document
    Added document for IP4220 dual USB port TVS chip
2014-10-17 Added document
    Added document for TPS2042 dual USB power switch
2014-10-17 Added document
    Added document for TUSB2077 7-port USB hub controller
2014-10-17 Schematic update
    Added NAND flash and all required signals. Also did a bit of rearranging
    and fencing of different gates.
2014-10-18 Added document
    Added document for FCI surface mount HDMI connector
2014-10-19 Added document
    Added document for the 3-port USB connector
2014-10-19 Schematic update
    Added HC-05-EZ part as well as the USB hub and necessary connectors etc.
2014-10-20 Added document
    Added document for the HC-05 module
2014-10-20 Schematic update
    Updated the HDMI differential pair names in schematic
2014-10-20 Added board
    Began routing HDMI signals

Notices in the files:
parts and their libraries:
SparkFun-Passives: Licensing: Creative Commons ShareAlike 4.0 International - https://creativecommons.org/licenses/by-sa/4.0
SparkFun-Aesthetics: Released under the Creative Commons
SparkFun-Aesthetics: https://creativecommons.org/licenses/by-sa/4.0
